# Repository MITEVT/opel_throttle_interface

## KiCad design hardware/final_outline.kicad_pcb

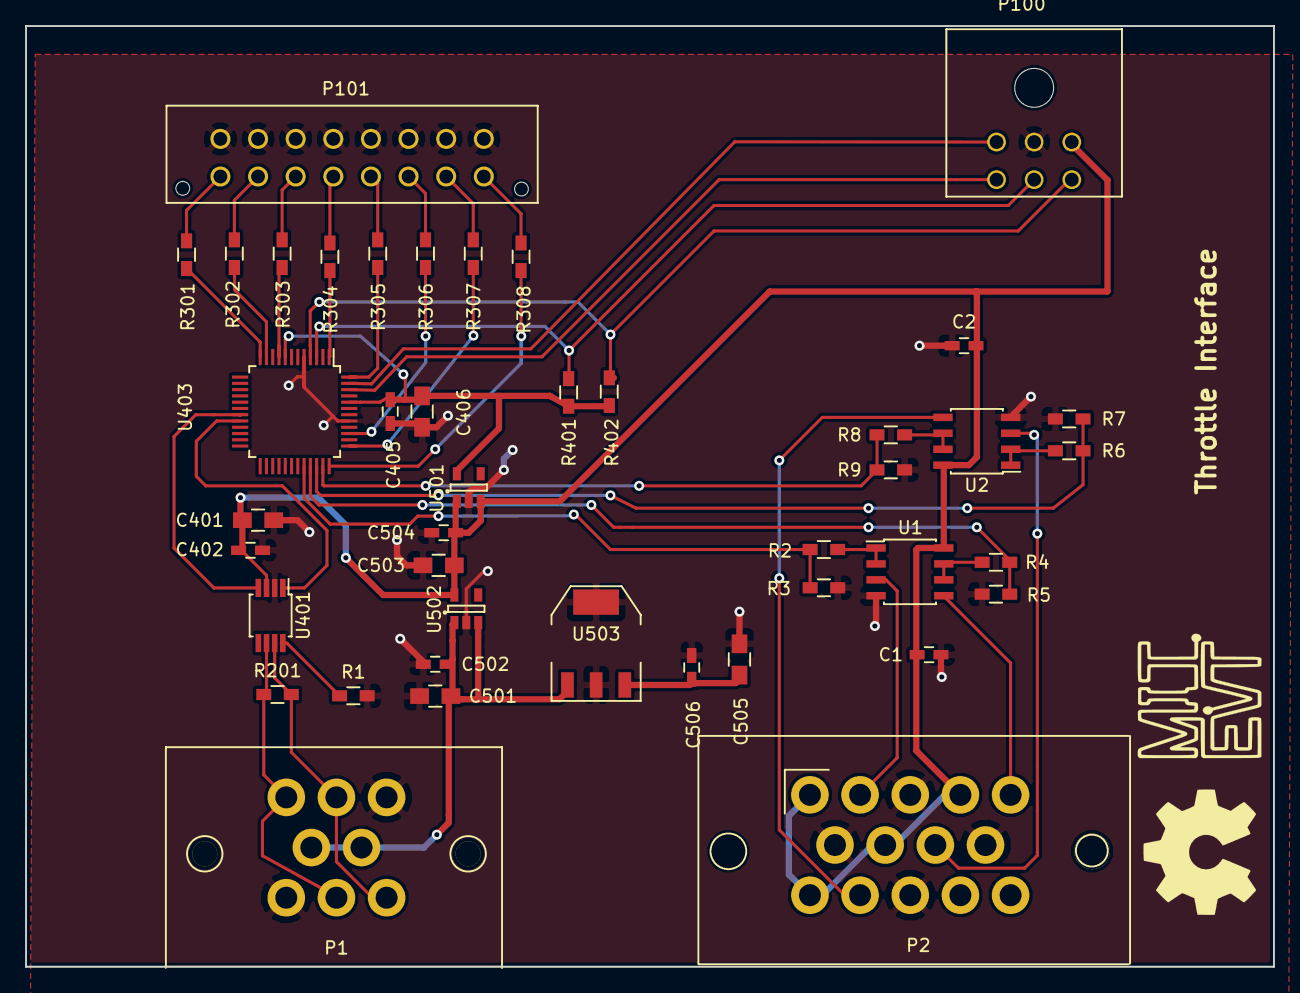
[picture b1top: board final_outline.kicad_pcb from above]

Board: 2 copper layers, 99.5 x 75.0 mm, 43 parts (0 on the bottom side), 42 nets.

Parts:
C1, C2: 1μ; C_0603_HandSoldering
C401, C406: 10uF; C_0805_HandSoldering
C402, C405: 0.1uF; C_0603_HandSoldering
C501, C503, C505: 10μ; C_0805_HandSoldering
C502, C504, C506: .1μ; C_0603_HandSoldering
P1: CANCONNECTOR; 776280-1
P2: CONN_01X14; 776267-1
P100: ISP; Connector_Microfit3_Header_02x03_Angled_43045-060x
P101: DEBUG_LED; Connector_Microfit3_Header_02x08_Straight_43045-1628
R1: 20k; R_0603_HandSoldering
R2, R4, R6, R8: 33k; R_0603_HandSoldering
R3, R5, R7, R9: 47k; R_0603_HandSoldering
R201: R; R_0603_HandSoldering
R301, R302, R303, R304, R305, R306, R307, R308: 100; R_0603_HandSoldering
R401, R402: 10k; R_0603_HandSoldering
U1, U2: LM358N; SOIC-8_3.9x4.9mm_Pitch1.27mm
U401: MCP2551-I/SN; MSOP-8_3x3mm_Pitch0.65mm
U403: LPC11C14; LQFP-48_7x7mm_Pitch0.5mm
U501: MCP1755-33; SOT-23-5
U502: MCP1755-5; SOT-23-5
U503: Zsr1000gta; SOT-223

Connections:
+3V3: C405.1, C406.1, R401.1, R402.1, U403.8, U403.44, U501.5
+5V: C1.2, C2.2, C401.1, C402.1, C503.1, C504.1, P2.1, P2.4, P2.7, P2.10, P100.3, U1.8, U2.8, U401.3, U501.1, U501.3, U502.5
+12V: C501.2, C502.1, P1.4, P1.5, U502.1, U502.3, U503.1
/BACK_PANEL/CANH: P1.2, P1.8, R201.2, U401.7
/BACK_PANEL/CANL: P1.1, P1.7, R201.1, U401.6
/BACK_PANEL/TPS1_5V: P2.2, U1.3
/BACK_PANEL/TPS2_5V: P2.5, U1.5
/BACK_PANEL/TPS3_5V: P2.8, U2.3
/BACK_PANEL/TPS4_5V: P2.11, U2.5
/FRONT_PANEL/LED0: R301.1, U403.12
/FRONT_PANEL/LED1: R302.2, U403.11
/FRONT_PANEL/LED2: R303.2, U403.9
/FRONT_PANEL/LED3: R304.1, U403.1
/FRONT_PANEL/LED4: R305.2, U403.48
/FRONT_PANEL/LED5: R306.1, U403.39
/FRONT_PANEL/LED6: R307.2, U403.37
/FRONT_PANEL/LED7: R308.1, U403.36
/FRONT_PANEL/MCU_PROG_N: P100.6, R402.2, U403.4
/FRONT_PANEL/MCU_RESET_N: P100.5, R401.2, U403.3
/FRONT_PANEL/RXD: P100.4, U403.46
/FRONT_PANEL/TXD: P100.1, U403.47
/Micro_Controller/CAN_RXD: U401.4, U403.19
/Micro_Controller/CAN_TXD: U401.1, U403.20
/Micro_Controller/TPS1_3.3V: R2.2, R3.1, U403.32
/Micro_Controller/TPS2_3.3V: R4.2, R5.1, U403.33
/Micro_Controller/TPS3_3.3V: R6.2, R7.1, U403.34
/Micro_Controller/TPS4_3.3V: R8.2, R9.1, U403.35
GND: C1.1, C2.1, C401.2, C402.2, C405.2, C406.2, C501.1, C502.2, C503.2, C504.2, C505.1, C506.1, P1.3, P1.6, P2.3, P2.6, P2.9, P2.12, P100.2, P101.1, P101.2, P101.3, P101.4, P101.5, P101.6, P101.7, P101.8, R1.2, R3.2, R5.2, R7.2, R9.2, U1.4, U2.4, U401.2, U403.5, U403.41, U501.2, U502.2, U503.2, U503.4
unnamed: P101.9, R301.2
unnamed: P101.10, R302.1
unnamed: P101.11, R303.1
unnamed: P101.12, R304.2
unnamed: P101.13, R305.1
unnamed: P101.14, R306.2
unnamed: P101.15, R307.1
unnamed: P101.16, R308.2
unnamed: R1.1, U401.8
unnamed: R2.1, U1.1, U1.2
unnamed: R4.1, U1.6, U1.7
unnamed: R6.1, U2.1, U2.2
unnamed: R8.1, U2.6, U2.7
VCC: C505.2, C506.2, U503.3

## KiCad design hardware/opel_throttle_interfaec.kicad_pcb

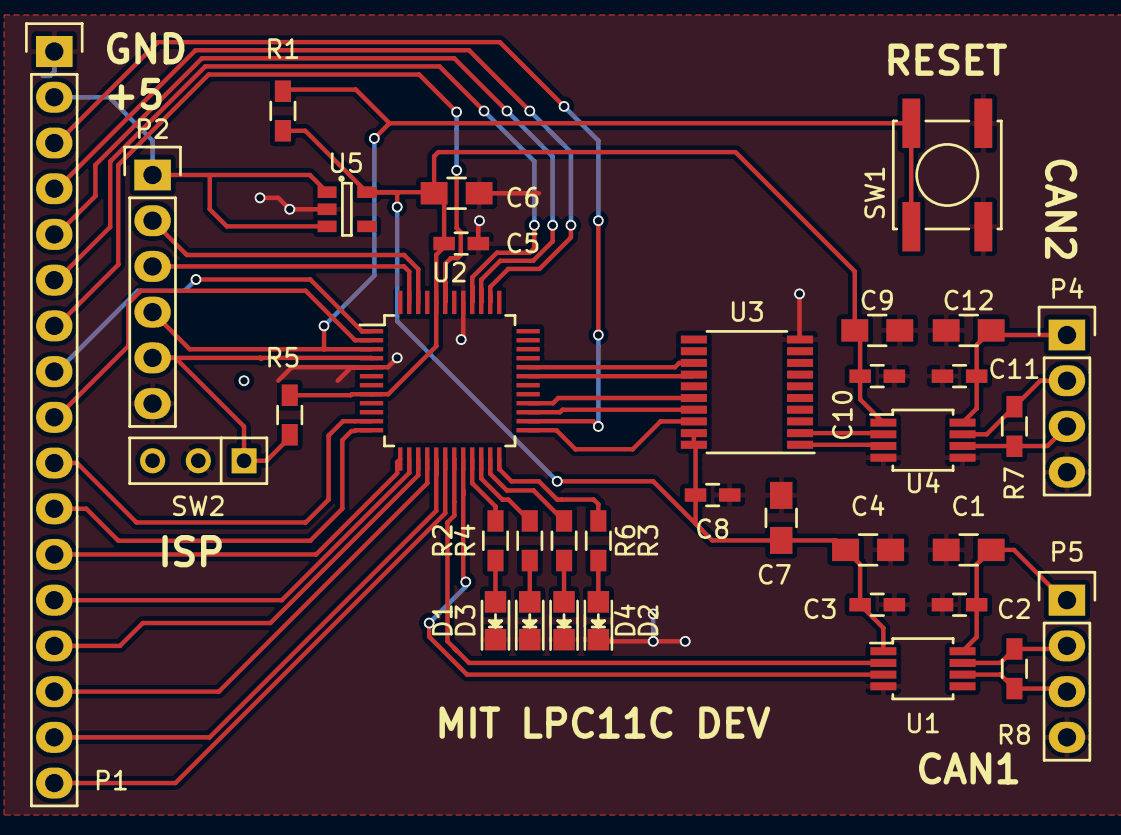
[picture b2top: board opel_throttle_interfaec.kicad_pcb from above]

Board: 2 copper layers, 35 parts (0 on the bottom side), 45 nets.

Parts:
C1, C4: 10uF; C_0805_HandSoldering
C2, C3, C5, C8, C10, C11: 0.1uF; C_0603_HandSoldering
C6: 1=uF; C_0805_HandSoldering
C7, C9, C12: 1uF; C_0805_HandSoldering
D1, D2, D3, D4: LED; LED-0805
P1: CONN_01X17; Pin_Header_Straight_1x17
P2: CONN_01X06; Pin_Header_Straight_1x06
P4, P5: CONN_01X04; Pin_Header_Straight_1x04
R1, R5: 10k; R_0603_HandSoldering
R2, R3, R4, R6: 100; R_0603_HandSoldering
R7, R8: 120; R_0603_HandSoldering
SW1: SPST; SW_SPST_EVPBF
SW2: SPST; SW_Micro_SPST
U1, U4: ISO1050; MSOP-8_3x3mm_Pitch0.65mm
U2: LPC11C14; LQFP-48_7x7mm_Pitch0.5mm
U3: MCP2515_TSSOP; TSSOP-20_4.4x6.5mm_Pitch0.65mm
U5: MCP1755; SOT-23-5

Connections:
+3V3: C3.1, C4.1, C5.1, C6.1, C7.1, C8.1, C9.1, C10.1, R1.1, R5.1, U1.1, U2.8, U2.44, U3.19, U3.20, U4.1, U5.5
+5V: P1.2, P2.1, U5.1, U5.3
/Input Connectors/MCU_PROG_N: P2.5, R5.2, SW2.1, U2.4
/Input Connectors/MCU_RESET_N: P2.4, R1.2, SW1.1, U2.3
/Input Connectors/RXD: P2.2, U2.46
/Input Connectors/TXD: P2.3, U2.47
/Micro Controller/CAN1H: P5.2, R8.1, U1.7
/Micro Controller/CAN1L: P5.3, R8.2, U1.6
/Micro Controller/CAN1P: C1.1, C2.1, P5.1, U1.8
/Micro Controller/CAN2H: P4.2, R7.1, U4.7
/Micro Controller/CAN2L: P4.3, R7.2, U4.6
/Micro Controller/CAN2P: C11.1, C12.1, P4.1, U4.8
/Micro Controller/PIO0_1: P1.9, U2.2
/Micro Controller/PIO0_3: P1.13, U2.14
/Micro Controller/PIO0_4: P1.14, U2.15
/Micro Controller/PIO0_5: P1.15, U2.16
/Micro Controller/PIO0_11: U2.32, U3.13
/Micro Controller/PIO1_3: P1.5, U2.39
/Micro Controller/PIO1_4: P1.6, U2.40
/Micro Controller/PIO1_9: P1.16, U2.17
/Micro Controller/PIO2_1: P1.12, U2.13
/Micro Controller/PIO2_2: P1.3, U2.26
/Micro Controller/PIO2_3: P1.4, U2.38
/Micro Controller/PIO2_4: P1.17, U2.18
/Micro Controller/PIO2_6: P1.8, U2.1
/Micro Controller/PIO2_7: P1.10, U2.11
/Micro Controller/PIO2_8: P1.11, U2.12
/Micro Controller/PIO3_2: P1.7, U2.43
GND: C1.2, C2.2, C3.2, C4.2, C5.2, C6.2, C7.2, C8.2, C9.2, C10.2, C11.2, C12.2, D1.1, D2.1, D3.1, D4.1, P1.1, P2.6, P4.4, P5.4, SW1.2, SW2.2, U1.4, U2.5, U2.41, U3.10, U4.4, U4.5, U5.2
unnamed: D1.2, R2.2
unnamed: D2.2, R3.2
unnamed: D3.2, R4.2
unnamed: D4.2, R6.2
unnamed: R2.1, U2.21
unnamed: R3.1, U2.24
unnamed: R4.1, U2.22
unnamed: R6.1, U2.23
unnamed: U1.2, U2.19
unnamed: U1.3, U2.20
unnamed: U2.25, U3.18
unnamed: U2.27, U3.17
unnamed: U2.28, U3.16
unnamed: U2.31, U3.14
unnamed: U3.1, U4.3
unnamed: U3.2, U4.2

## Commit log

2015-10-24 Added first schematic for throttle interface
2015-10-28 initial commit for TI; CAN spec
2015-10-31 main.c: added TPS redundancy logic ; board.c: migrated functions from main.c
2016-01-13 firmware: fixed ADC code
2016-01-16 hardware: initial commit
2016-01-16 hardware: TPS level converter; firmware: some updates to the ADC code, still need to fix
2016-01-30 making sure i know
2016-02-06 hardware: begain board layout
2016-02-27 still need to swap out connector
2016-06-16 throttle interface pcb with additional TPS level converters
2016-06-16 ADC functionality with motor interface
2017-01-14 Complying to CAN spec for frequency
